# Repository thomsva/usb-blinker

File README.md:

# USB powered blinking led - practice project

Blinks a led using power from USB-C cable.

## Features

- Takes 5V from USB port by connecting CC1 and CC2 to ground trough 5.1k resistors. 
- Led powered direcly from TLC555 power

## License

This project is licensed under the [MIT License](LICENSE).

## Preview

*Top view*

*Bottom view*

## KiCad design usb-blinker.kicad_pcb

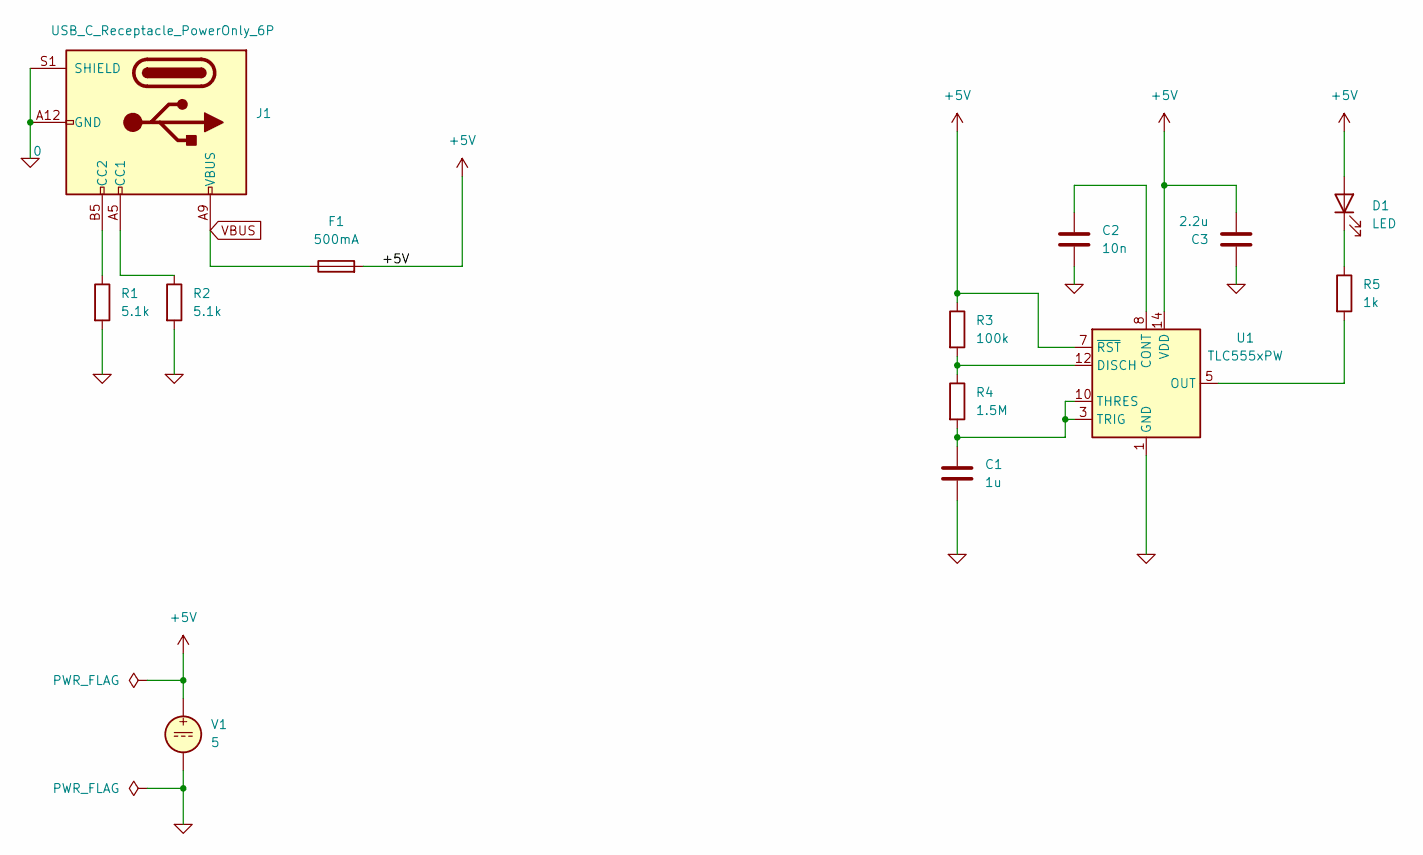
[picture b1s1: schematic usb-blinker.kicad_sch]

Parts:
C1: 1u; C_0603_1608Metric
C2: 10n; C_0603_1608Metric
C3: 2.2u; C_0603_1608Metric
D1: LED; LED_0603_1608Metric
F1: 500mA; Fuse_0603_1608Metric
J1: USB_C_Receptacle_PowerOnly_6P; USB_C_Receptacle_GCT_USB4125-xx-x-0190_6P_TopMnt_Horizontal
R1, R2: 5.1k; R_0603_1608Metric
R3: 100k; R_0603_1608Metric
R4: 1.5M; R_0603_1608Metric
R5: 1k; R_0603_1608Metric
U1: TLC555xPW; TSSOP-14_4.4x5mm_P0.65mm
V1: 5

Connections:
0: C1.2, C2.2, C3.1, J1.A12 (GND), J1.B12 (GND), J1.S1 (SHIELD), R1.2, R2.2, U1.1 (GND), V1.2
+5V: C3.2, D1.2 (A), F1.2, R3.1, U1.7 (~RST), U1.14 (VDD), V1.1
unnamed: D1.1 (K), R5.1
unnamed: J1.A5 (CC1), R2.1
unnamed: J1.B5 (CC2), R1.1
unnamed: C2.1, U1.8 (CONT)
unnamed: R3.2, R4.1, U1.12 (DISCH)
unnamed: R5.2, U1.5 (OUT)
unnamed: C1.1, R4.2, U1.3 (TRIG), U1.10 (THRES)
VBUS: F1.1, J1.A9 (VBUS), J1.B9 (VBUS)

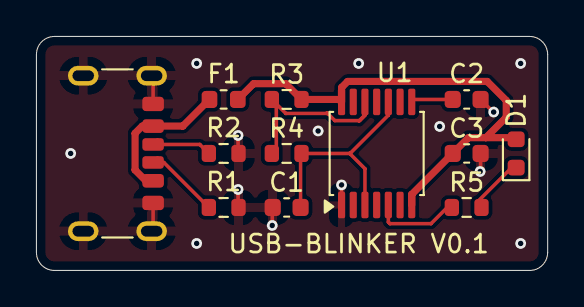
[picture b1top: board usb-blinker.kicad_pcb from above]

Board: 2 copper layers, 28.4 x 13.0 mm, 12 parts (0 on the bottom side), 10 nets.

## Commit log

2026-03-06 latest changes
2026-03-06 added fuse, pcb remake
2026-03-11 added workflow and images
2026-03-11 added erc and drc badges
2026-03-11 update to ignore autosave correctly
2026-03-11 wider power traces
2026-03-11 created new images
2026-03-11 layout and pcb corner radius
2026-03-11 generated new images
2026-03-11 changed zoom for 3d image
2026-03-11 update images
2026-03-11 images
2026-03-11 edited pcb traces
2026-03-29 added .history to gitignore
2026-03-29 using Interactive Html Bom plugin
2026-03-29 Add MIT License to the project
